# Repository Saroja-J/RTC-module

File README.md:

# ⏰ Real-Time Clock (RTC) Module

## 📖 Overview

The **Real-Time Clock (RTC) Module** is designed around the **DS1307 RTC IC** to provide accurate timekeeping for embedded systems. It communicates with the host controller using the **I²C interface** and maintains time even when the main power supply is disconnected using a **CR2032 backup battery**.

In addition to real-time clock functionality, the module includes an **AT24CS01 EEPROM** for storing non-volatile configuration data and a **DS18B20 digital temperature sensor** interface for environmental monitoring.

---

## ✨ Features

- DS1307 Real-Time Clock
- CR2032 Backup Battery Support
- I²C Communication Interface
- 32.768 kHz Crystal Oscillator
- AT24CS01 I²C EEPROM
- DS18B20 Temperature Sensor Interface
- Power Status LED
- Compact and Expandable Design

---

## 🛠️ Hardware Components

| Component | Description | Datasheet |
|-----------|-------------|-----------|
| **DS1307** | Real-Time Clock (RTC) IC with battery backup | [📄 DS1307 Datasheet](https://www.alldatasheet.com/datasheet-pdf/view/254791/MAXIM/DS1307.html) |
| **32.768 kHz Crystal** | Provides accurate clock reference for the RTC | N/A |
| **CR2032 Battery** | 3V Lithium Coin Cell for RTC backup power | [📄 CR2032 Datasheet](https://www.alldatasheet.com/datasheet-pdf/view/95177/SONY/CR2032.html) |
| **AT24C32 EEPROM** | 32-Kbit I²C Serial EEPROM for non-volatile data storage | [📄 AT24C32 Datasheet](https://www.alldatasheet.com/datasheet-pdf/view/56067/ATMEL/AT24C32.html) |
| **DS18B20** | Digital 1-Wire Temperature Sensor | [📄 DS18B20 Datasheet](https://www.alldatasheet.com/datasheet-pdf/view/1244260/MAXIM/DS18B20.html) |
| **Pull-up Resistors** | Required for stable I²C communication | N/A |
| **Power LED** | Indicates board power status | N/A |

---

## 📷 Schematic

---

## 🏗️ Hardware Architecture

```
```
## ⚡ Power Specifications

| Parameter | Value |
|----------|-------|
| Input Voltage | 5V |
| Backup Voltage | 3V (CR2032) |
| Communication | I²C |

---

## 📋 Applications

- Data Logging
- IoT Devices
- Smart Home Automation
- Industrial Controllers
- Attendance Systems
- Battery-backed Embedded Systems
- Time Scheduling Applications

---

## 📌 Design Highlights

- Battery-backed real-time clock
- External 32.768 kHz crystal for accurate timing
- Shared I²C bus for RTC and EEPROM
- Digital temperature monitoring
- Low component count
- Easy integration with ESP32

---

## 🚀 Future Improvements

- Upgrade to DS3231 for higher accuracy
- Add ESD protection
- Add reverse polarity protection
- Configurable EEPROM address selection

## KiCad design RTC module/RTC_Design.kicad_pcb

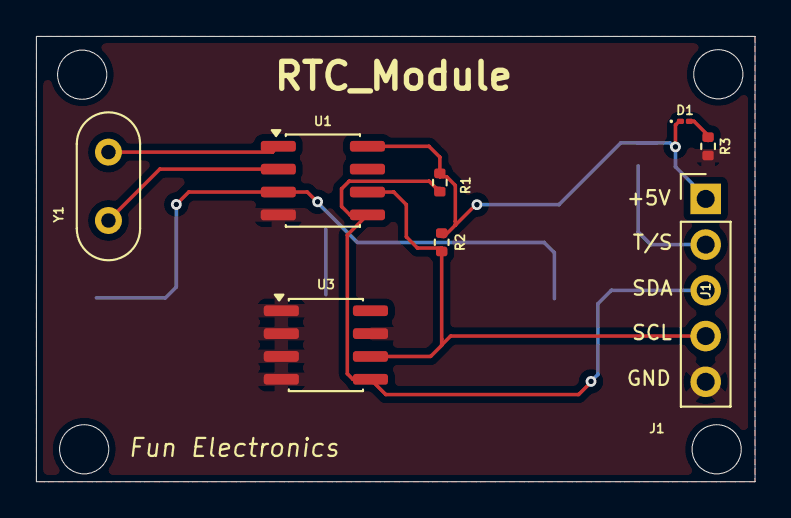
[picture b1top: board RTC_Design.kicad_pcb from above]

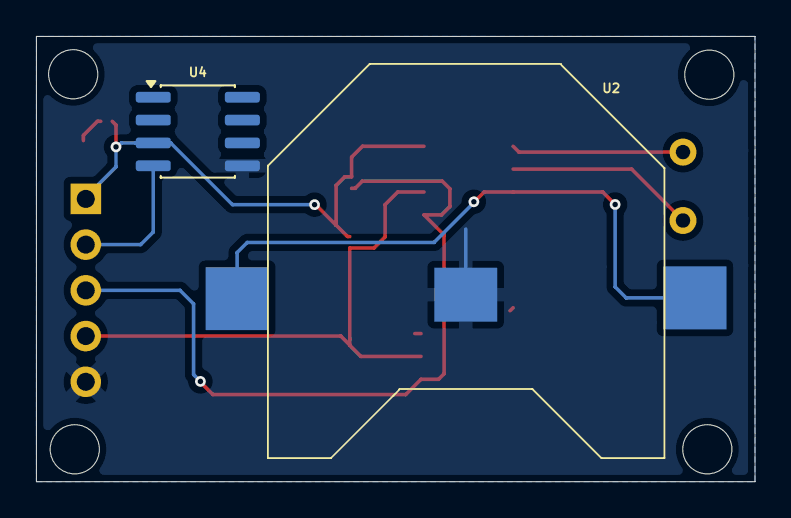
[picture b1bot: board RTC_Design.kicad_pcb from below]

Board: 2 copper layers, 39.9 x 24.7 mm, 10 parts (2 on the bottom side), 9 nets.

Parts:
D1: LED; LED_01005_0402Metric
J1: Conn_01x05_Socket; PinHeader_1x05_P2.54mm_Vertical
R1, R2, R3: R; R_0402_1005Metric
U1: DS1307Z+; SOIC-8_3.9x4.9mm_P1.27mm
U2: Conn_01x03_Pin; CR2032
U3: AT24CS01-SSHM; SOIC-8_3.9x4.9mm_P1.27mm
U4: DS18B20Z; SOIC-8_3.9x4.9mm_P1.27mm
Y1: Crystal; Crystal_HC52-8mm_Vertical

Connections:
+5V: D1.1 (K), J1.1, R1.1, R2.1, U1.8 (VCC), U4.3 (V_{DD})
/RTC_SCL: J1.4, R2.2, U1.6 (SCL), U3.6 (SCL)
/RTC_SDA: J1.3, R1.2, U1.5 (SDA), U3.5 (SDA)
/Temp_Sensor: J1.2, U4.4 (DQ)
GND: J1.5, R3.1, U1.4 (GND), U2.3, U3.1 (A0), U3.2 (A1), U3.3 (A2), U3.4 (GND), U3.7 (WP), U4.5 (GND)
unnamed: D1.2 (A), R3.2
unnamed: U1.3 (VBAT), U2.1, U2.2
unnamed: U1.1 (X1), Y1.2
unnamed: U1.2 (X2), Y1.1
